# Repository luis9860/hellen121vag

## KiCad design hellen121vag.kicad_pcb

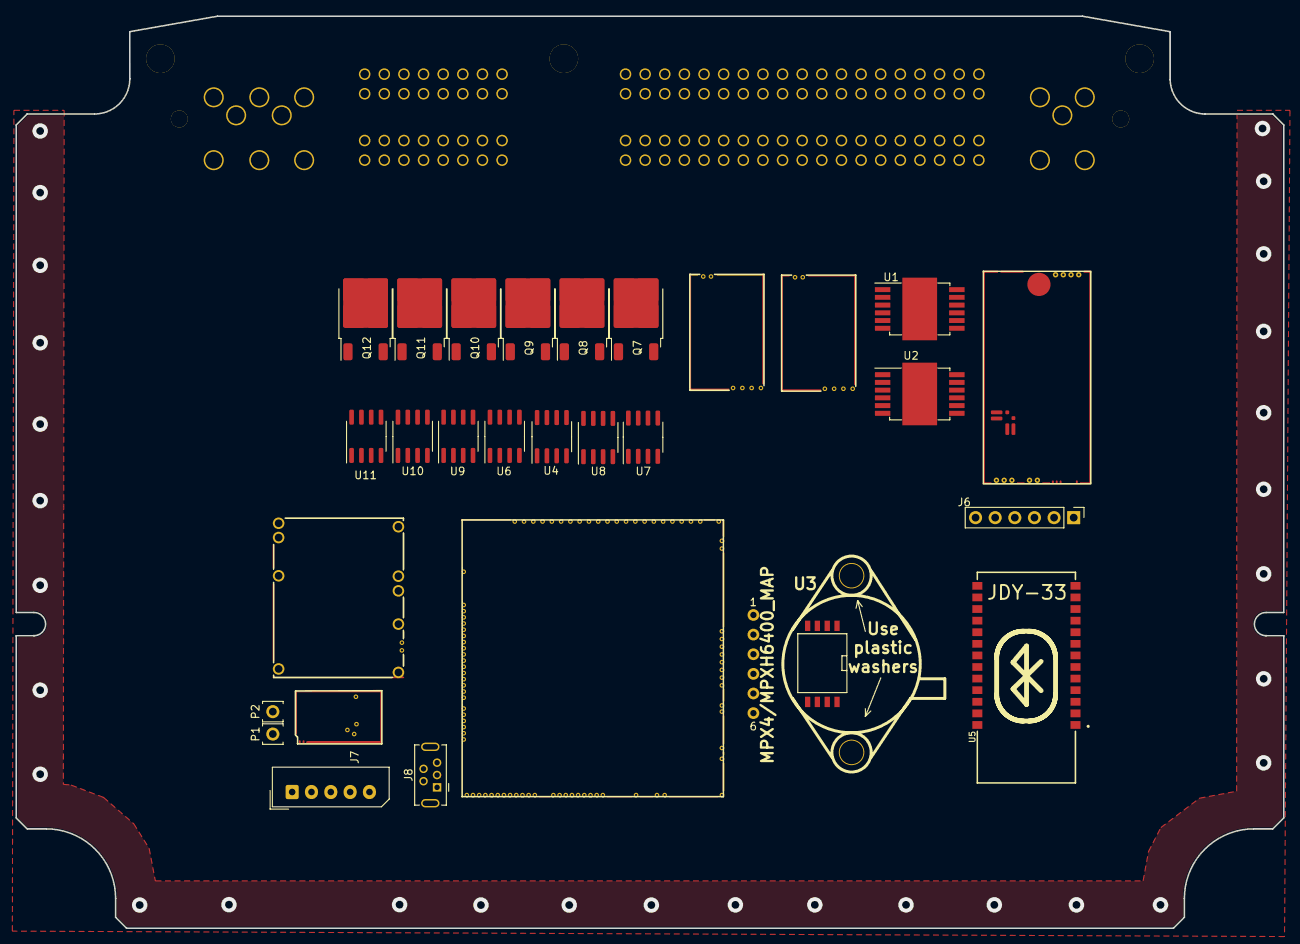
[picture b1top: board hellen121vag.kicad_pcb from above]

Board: 4 copper layers, 164.0 x 118.0 mm, 30 parts (1 on the bottom side), 6 nets, no tracks yet.

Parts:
G4: DISCLAIMER; Off_Road_Disclaimer
J6: Conn_01x06; PinHeader_1x06_P2.54mm_Vertical
J7: Conn_01x05_Male; Molex_SPOX_5267-05A_1x05_P2.50mm_Vertical
J8: USB_B_Mini; USB-MINI-B-VERTICAL
M1: Module-power_12and5V-0.3; power_12and5V
M3: Module-vr-discrete-0.5; vr-discrete
M4: Module-vr-max9924-0.1; vr-max9924
M5: Module-wbo-0.5; wbo
M6: Module:mega-mcu100/0.3; mega-mcu100
M7: Module-can-0.1; can
P1: 368255-2
P1#2, P2: Pad; PAD-TH
Q7, Q8, Q9, Q10, Q11, Q12: ISL9V3040D3ST; TO-252-2
U1, U2: TLE9201SG; Infineon_PG-DSO-12-11
U3: MPX4/MPXH6400_MAP; MPX-4_MAP
U4: MAX31855KASA; SOIC-8_3.9x4.9mm_P1.27mm
U5: JDY-33
U6, U7, U8, U9, U10, U11: VNLD5160TR-E; SOIC-8_3.9x4.9mm_P1.27mm

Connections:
+5V: M1.E4 (V5), M6.N22 (VCC)
+5VA: M3.E4 (V5_IN), M4.E4 (V5_IN), M5.W1 (V5_IN), M6.E1 (V5A_SWITCHABLE), M6.W2 (V5A_SWITCHABLE), M7.V1 (V5), U3.3 (VCC)
+12V_RAW: M1.V1 (V12_PERM), M1.V3 (V12_RAW)
/CAN+: M5.W4 (CANH), M6.W11 (CANH)
/CAN-: M5.W3 (CANL), M6.W12 (CANL)
GND: J6.3, J7.4, J7.5, J8.5 (GND), J8.6 (Shield), M1.S1 (GND), M3.G (GND), M4.G (GND), M5.E6 (LSU_H-), M5.G (GND), M6.G (GND), M7.E1 (GND), Q7.3 (E), Q8.3 (E), Q9.3 (E), Q10.3 (E), Q11.3 (E), Q12.3 (E), U1.6 (GND), U1.8 (SI), U1.9 (CSN), U1.10 (SCK), U1.13 (GND), U2.6 (GND), U2.8 (SI), U2.9 (CSN), U2.10 (SCK), U2.13 (GND), U3.2 (GND), U4.1 (GND), U5.13 (GND), U6.5 (S2), U6.7 (S1), U7.5 (S2), U7.7 (S1), U8.5 (S2), U8.7 (S1), U9.5 (S2), U9.7 (S1), U10.5 (S2), U10.7 (S1), U11.5 (S2), U11.7 (S1)

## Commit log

2025-12-05 [skip actions] Auto-generated board
2025-12-05 wewe
2025-12-05 wewewe
2025-12-08 test de conexion
